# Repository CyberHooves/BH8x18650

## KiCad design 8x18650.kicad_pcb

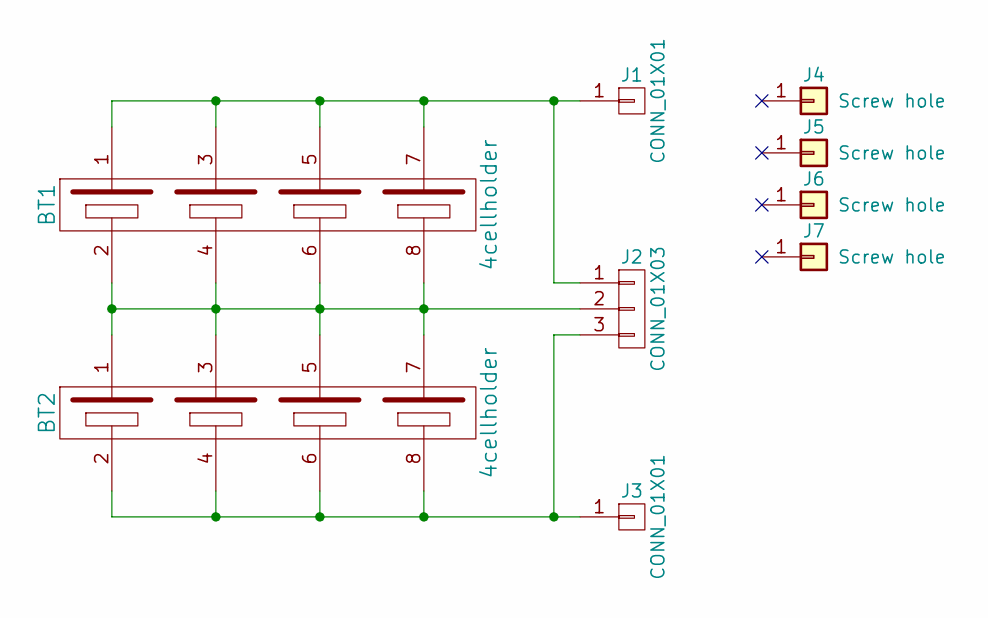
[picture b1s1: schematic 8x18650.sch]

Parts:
BT1, BT2: 4cellholder; BH-81650-4-1
J1, J3: CONN_01X01; MH-H3.2-P7
J2: CONN_01X03; JST_PH_B3B-PH-K_03x2.00mm_Straight
J4, J5, J6, J7: Screw hole; MH-H3.2-P7

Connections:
unnamed: BT1.1, BT1.3, BT1.5, BT1.7, J1.1, J2.1
unnamed: BT1.2, BT1.4, BT1.6, BT1.8, BT2.1, BT2.3, BT2.5, BT2.7, J2.2
unnamed: BT2.2, BT2.4, BT2.6, BT2.8, J2.3, J3.1

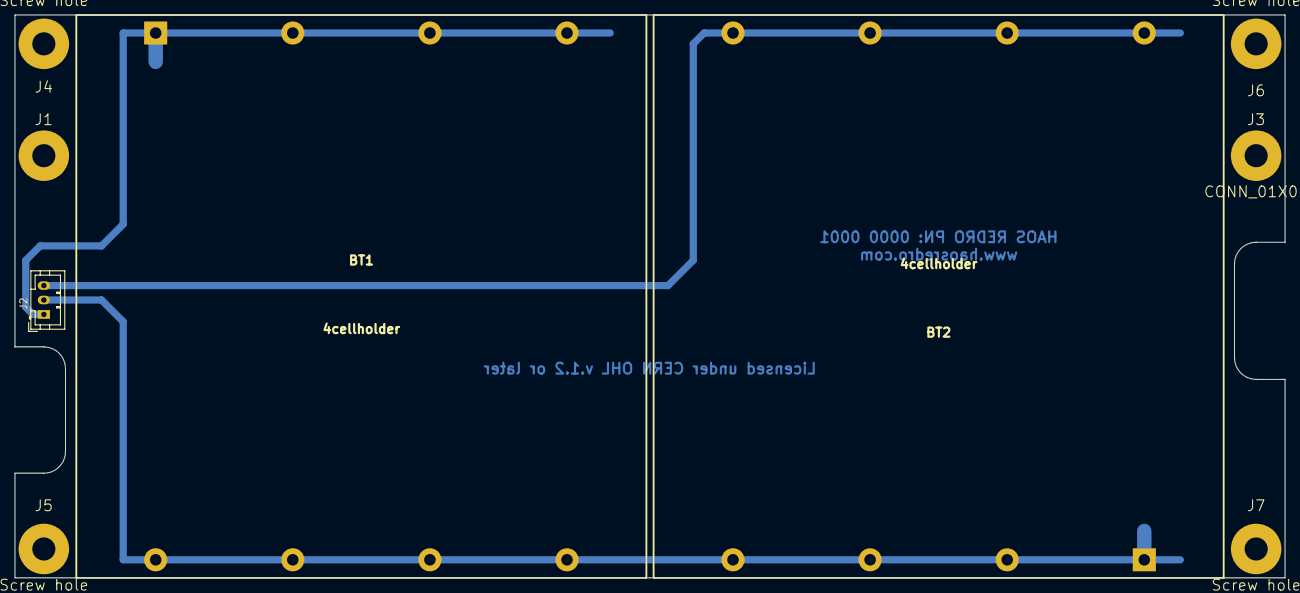
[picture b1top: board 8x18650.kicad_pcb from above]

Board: 2 copper layers, 176.0 x 78.0 mm, 9 parts (0 on the bottom side), 3 nets.

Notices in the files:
8x18650.kicad_pcb:
Licensed under CERN OHL v.1.2 or later
